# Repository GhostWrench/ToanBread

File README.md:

# Toan Bread

Repository for the ToanMachine bread board breakout board for guitar pedal prototyping.

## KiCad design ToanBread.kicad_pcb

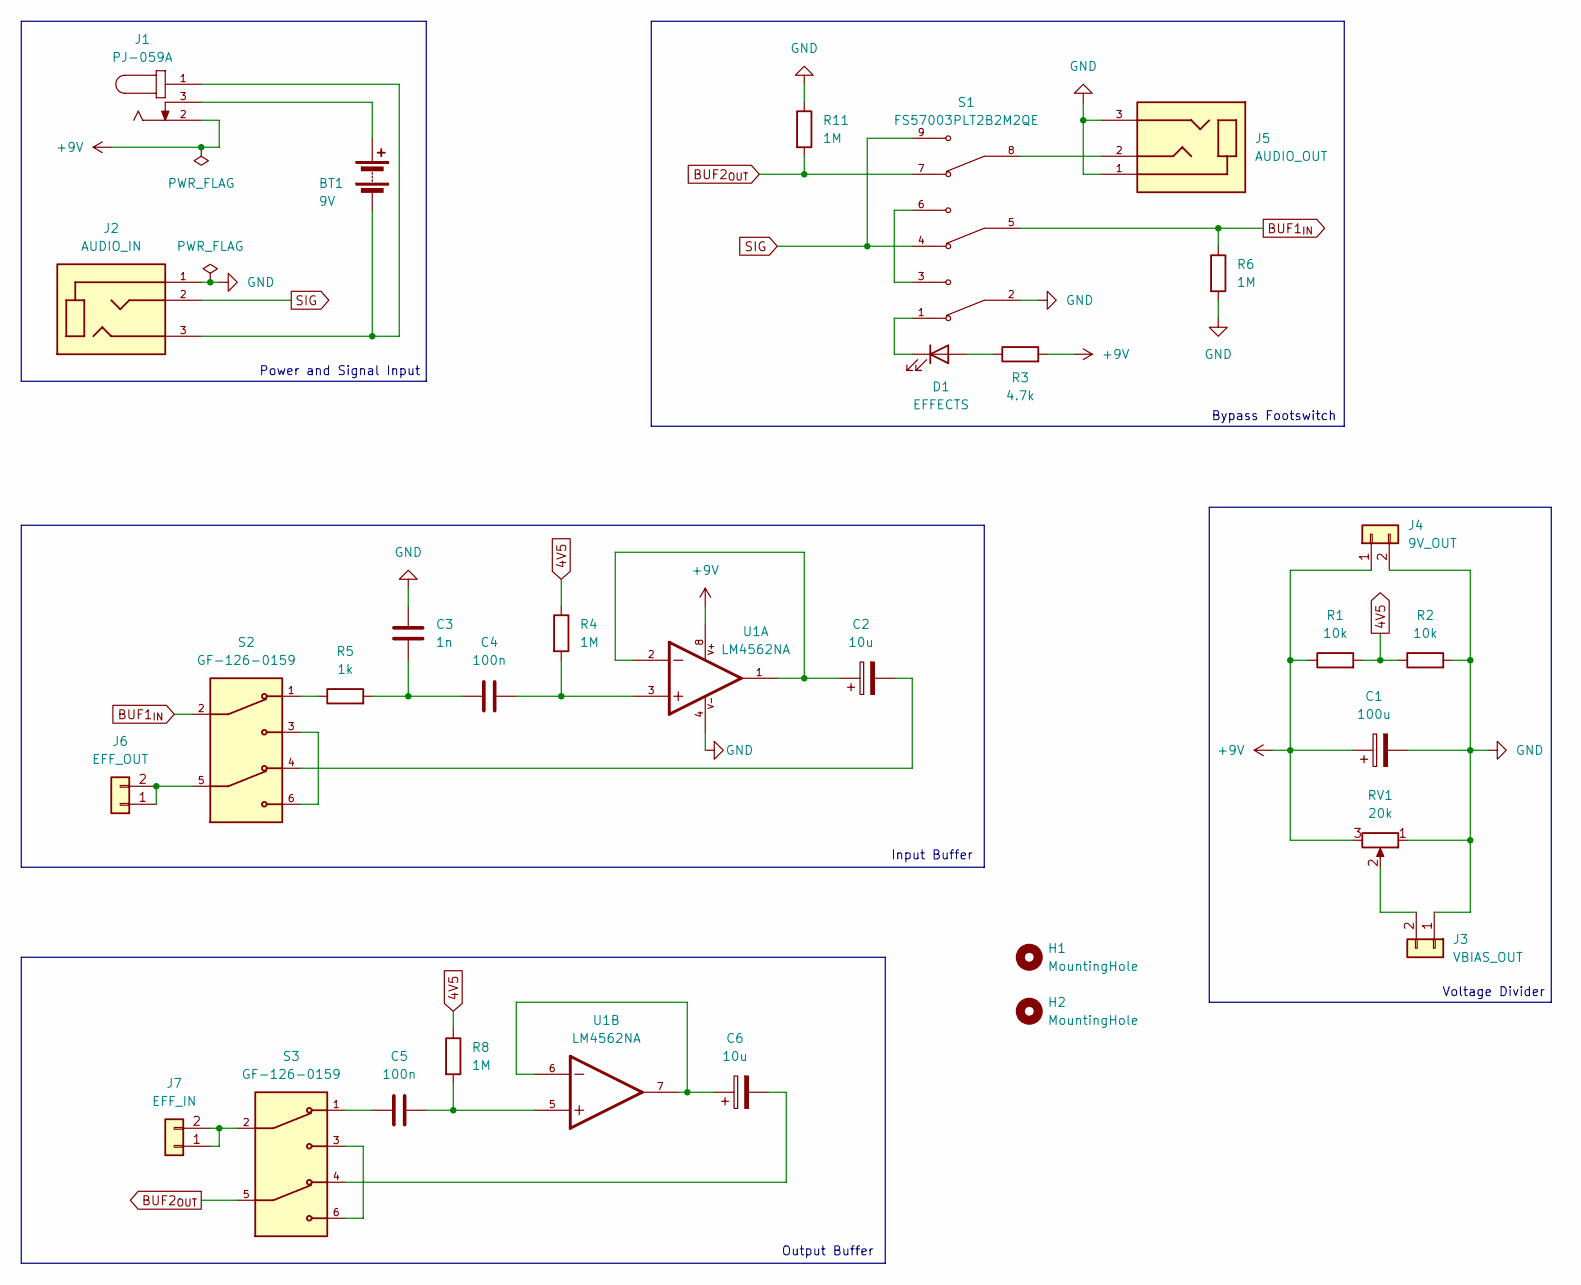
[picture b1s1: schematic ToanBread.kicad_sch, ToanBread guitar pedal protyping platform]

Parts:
BT1: 9V; PinHeader_1x02_P2.54mm_Vertical
C1: 100u; CP_Radial_D5.0mm_P2.00mm
C2, C6: 10u; CP_Radial_D5.0mm_P2.00mm
C3: 1n; C_Rect_L7.0mm_W2.5mm_P5.00mm
C4, C5: 100n; C_Rect_L7.0mm_W2.5mm_P5.00mm
D1: EFFECTS; LED_D5.0mm
H1, H2: MountingHole; MountingHole_3.2mm_M3_DIN965
J1: PJ-059A; CUI_PJ-059A; PARTREV 1.02
J2: AUDIO_IN; CUI_SJ-63053A; PARTREV 1.0
J3: VBIAS_OUT; PinHeader_1x02_P2.54mm_Vertical
J4: 9V_OUT; PinHeader_1x02_P2.54mm_Vertical
J5: AUDIO_OUT; CUI_SJ-63053A; PARTREV 1.0
J6: EFF_OUT; PinHeader_1x02_P2.54mm_Vertical
J7: EFF_IN; PinHeader_1x02_P2.54mm_Vertical
R1, R2: 10k; R_Axial_DIN0207_L6.3mm_D2.5mm_P7.62mm_Horizontal
R3: 4.7k; R_Axial_DIN0207_L6.3mm_D2.5mm_P7.62mm_Horizontal
R4, R6, R8, R11: 1M; R_Axial_DIN0207_L6.3mm_D2.5mm_P7.62mm_Horizontal
R5: 1k; R_Axial_DIN0207_L6.3mm_D2.5mm_P7.62mm_Horizontal
RV1: 20k; PTN16-A20120K1B1
S1: FS57003PLT2B2M2QE; SW_FS57003PLT2B2M2QE; PARTREV 4.2.2018
S2, S3: GF-126-0159; SW_GF-126-0159
U1: LM4562NA; DIP794W45P254L959H508Q8; PARTREV K

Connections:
4V5: R1.2, R2.1, R4.1, R8.1
+9V: C1.1, J1.2, J4.1, R1.1, R3.2, RV1.3, U1.8
BUF1_{IN}: R6.1, S1.5, S2.2
BUF2_{OUT}: R11.2, S1.7, S3.5
GND: C1.2, C3.1, J2.1, J3.1, J4.2, J5.1, J5.3, R2.2, R6.2, R11.1, RV1.1, S1.2, U1.4
unnamed: BT1.1 (+), J1.3
unnamed: BT1.2 (-), J1.1, J2.3
unnamed: C2.1, U1.1, U1.2
unnamed: C2.2, S2.4
unnamed: C3.2, C4.1, R5.2
unnamed: C4.2, R4.2, U1.3
unnamed: C5.1, S3.1
unnamed: C5.2, R8.2, U1.5
unnamed: C6.1, U1.6, U1.7
unnamed: C6.2, S3.4
unnamed: D1.2 (A), R3.1
unnamed: D1.1 (K), S1.1
unnamed: J3.2, RV1.2
unnamed: J5.2, S1.8
unnamed: J6.1, J6.2, S2.5
unnamed: J7.1, J7.2, S3.2
unnamed: R5.1, S2.1
unnamed: S1.3, S1.6
unnamed: S2.3, S2.6
unnamed: S3.3, S3.6
SIG: J2.2, S1.4, S1.9

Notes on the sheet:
Power and Signal Input
Input Buffer
Output Buffer
Bypass Footswitch
Voltage Divider

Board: 2 copper layers, 30 parts (4 on the bottom side), 26 nets, no tracks yet.

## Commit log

2024-04-02 Add README
2024-04-02 Add KiCAD specific .gitignore
2024-04-02 Add project specific part libraries
2024-04-02 Add initial power and bypass circuitry
2024-04-04 Add LTSpice model of the input buffer
2024-04-04 Associate most components
2024-04-04 Add custom PTN16-A20120K1B1 pot footprint
2024-04-04 Complete initial v0.3 board layout
2024-04-04 First pass at pcb layout
2024-04-04 Add info and logo to silkscreen
2024-04-11 Final updates to the v0.3 board
2024-04-11 Generate Gerbers for v0.3
2024-04-18 Fix resistor footprints
2024-04-18 Make footswitch pads bigger
2024-04-20 Fix input and output buffer switches
